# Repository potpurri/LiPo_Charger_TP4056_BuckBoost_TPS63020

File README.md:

# Lithium Battery Charger and Boost Converter PCB

This PCB is designed to safely charge a lithium-ion cell and provide a selectable 3.3V or 5V output. It's equipped with components that ensure safe charging and protection for the battery and supports flexible output and charging options. 

## Features

- **Charging IC**: TP4056 with adjustable charge currents.
- **Protection Circuitry**: DW01A and F8205A provide overcharge, over-discharge, and overcurrent protection.
- **Buck-Boost Converter**: TPS63020 for stable 3.3V or 5V output, selectable via solder jumper.
- **Compact Design**: Ideal for portable applications, with both top and bottom images of the board for easy identification.
- **Fuse Protection**: Added fuse for enhanced safety of the battery connection.
- **Battery disconnection during charging**: When the USB-C port is connected for charging, the battery is disconnected from the Buck-Boost converter via two p-channel MOSFETs in series, with the gates tied to VBUS of the USB-C input. Power is instead provided to the Buck-Boost converter using a Schottky diode during charging. This circuit can be bypassed using the solder jumper on the bottom side of the PCB.

## Charging Current Settings

The charging current of the TP4056 can be adjusted using solder jumpers on the PCB to meet various requirements. Refer to the table below:

| Solder Jumper Setting | Charging Current |
|-----------------------|------------------|
| J1                    | 130 mA           |
| J2                    | 280 mA           |
| J3                    | 400 mA           |
| J4                    | 580 mA           |
| J5                    | 780 mA           |
| J6                    | 1000 mA          |

## Images

### Schematic

### 3D Renderings
- Front View: 
- Front View Without Components: 
- Back View: 

### PCB
**4-Layer Stackup**: Signal Layer, GND Layer, Power Layer, Signal Layer
- All layers: 
- Front traces: 
- GND plane: 
- PWR plane: 
- Back traces: 

## Usage

1. **Output Voltage Selection**: Set the desired output voltage (3.3V or 5V) by configuring the solder jumper on the PCB.
2. **Charging Current Selection**: Set the charging current by adjusting the appropriate solder jumper(s) according to the table above.
3. **Connect Battery**: Connect the lithium-ion cell to the battery terminals.
4. **Power Input**: Provide power via the charging input, and the circuit will manage safe charging for the battery and maintain output stability.
5. **Fuse Protection**: Ensure the fuse is correctly in place for additional battery safety.
6. **Battery disconnection during charging**: When the USB-C port is connected, the battery is safely disconnected from the Buck-Boost converter, and power is instead supplied to it from VBUS through a Schottky diode.

---

This board is ideal for applications needing a stable 3.3V or 5V from a lithium-ion cell with enhanced safety and flexibility. With the added features, it provides even more robust protection and usability for various portable electronic projects.

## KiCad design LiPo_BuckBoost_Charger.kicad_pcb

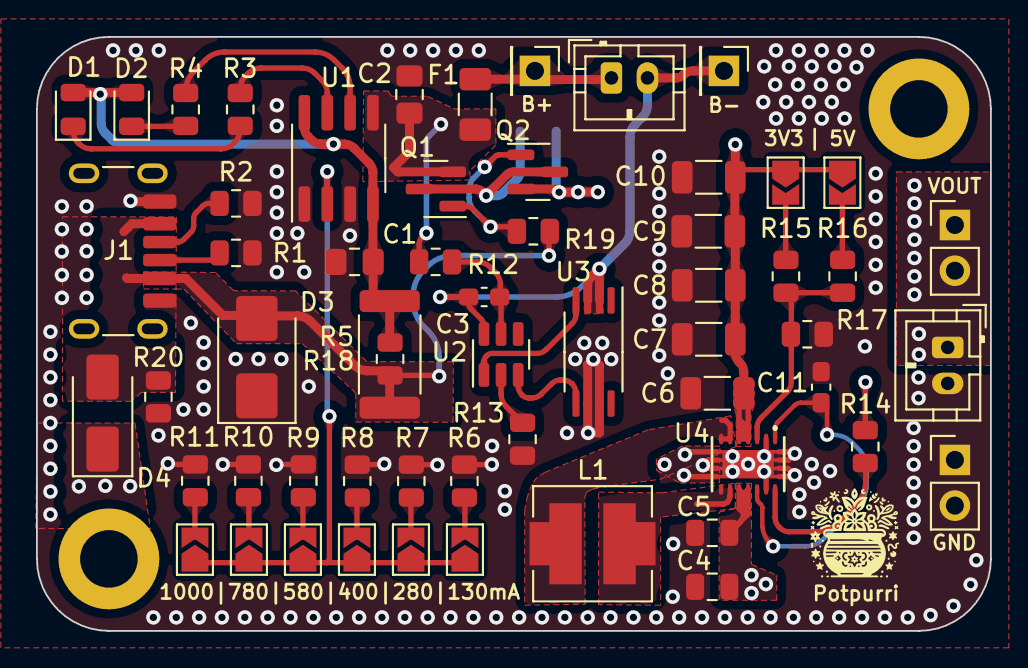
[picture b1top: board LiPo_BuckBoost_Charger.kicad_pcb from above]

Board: 4 copper layers, 53.0 x 33.0 mm, 61 parts (1 on the bottom side), 34 nets.

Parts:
C1, C2: 10u; C_0805_2012Metric_Pad1.18x1.45mm_HandSolder
C3, C11: 100n; C_0603_1608Metric_Pad1.08x0.95mm_HandSolder
C4, C5: 10u; C_0805_2012Metric
C6, C7, C8, C9: 22u; C_1206_3216Metric
C10: 100u; C_1206_3216Metric
D1: RED; D_0805_2012Metric
D2: GREEN; D_0805_2012Metric
D3: SMBJ12CA; D_SMB
D4: SS34; D_SMA
F1: 1.5A; Fuse_1206_3216Metric
H1, H2: MountingHole; MountingHole_3.2mm_M3_DIN965_Pad
J1: Type-C_6P; USB-C 6 Pin - Long pads
J2, J5: JST PH Connector; JST_PH_B2B-PH-K_1x02_P2.00mm_Vertical
J3, J4: Conn_01x01; PinHeader_1x01_P2.54mm_Vertical
J6, J7: JST PH Connector; PinHeader_1x02_P2.54mm_Vertical
JP1, JP2, JP3, JP4, JP5, JP6, JP7, JP8: SolderJumper_2_Open; SolderJumper-2_P1.3mm_Open_TrianglePad1.0x1.5mm
JP9: SolderJumper_3_Open; SolderJumper-3_P2.0mm_Open_TrianglePad1.0x1.5mm
L1: 2u2; Combined CD43 + L 6.3x6.3
Q1, Q2: SI2301; SOT-23
R1, R2: 5k1; R_0805_2012Metric
R3, R4, R13: 1k; R_0805_2012Metric
R5: 0R4; R_0805_2012Metric
R6, R20: 10k; R_0805_2012Metric
R7: 4k7; R_0805_2012Metric
R8: 3k; R_0805_2012Metric
R9: 2k; R_0805_2012Metric
R10: 1k5; R_0805_2012Metric
R11: 1k2; R_0805_2012Metric
R12: 100R; R_0805_2012Metric
R14, R15: 1M; R_0805_2012Metric
R16: 1M6; R_0805_2012Metric
R17: 180k; R_0805_2012Metric
R18: 2512 package; R_2512_6332Metric
R19: R; R_0805_2012Metric
U1: TP4056; SOP-8_3.76x4.96mm_P1.27mm
U2: DW01A; SOT-23-6
U3: FS8205A; TSSOP-8_4.4x3mm_P0.65mm
U4: TPS63020; QFN14-3X4MM

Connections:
+5V: C6.1, C7.1, C8.1, C9.1, C10.1, J5.1, J6.1, J6.2, JP7.1 (A), JP8.1 (A), R14.1, U4.4 (VOUT), U4.5 (VOUT)
+BATT: F1.1, J2.1, J3.1
-BATT: C3.2, J2.2, J4.1, U2.6 (GND), U3.2 (S1), U3.3 (S1)
GND: C1.2, C2.2, C4.2, C5.2, C6.2, C7.2, C8.2, C9.2, C10.2, C11.2, D3.1 (A1), J1.A12 (GND), J1.B12 (GND), J5.2, J7.1, J7.2, R1.2, R2.2, R6.2, R7.2, R8.2, R9.2, R10.2, R11.2, R13.2, R17.2, R20.2, U1.1 (TEMP), U1.3 (GND), U3.6 (S2), U3.7 (S2), U4.2 (GND), U4.13 (PS/SYNC), U4.15 (PGND), U4.16 (PGND), U4.17 (PGND), U4.18 (PGND), U4.19 (PGND), U4.20 (PGND), U4.21 (PGND), U4.22 (PGND), U4.23 (PGND)
unnamed: C1.1, D1.2 (A), D2.2 (A), R5.1, R18.1, U1.4 (VCC), U1.8 (CE)
unnamed: D1.1 (K), R3.1
unnamed: D2.1 (K), R4.1
unnamed: J1.A5 (CC1), R2.1
unnamed: J1.B5 (CC2), R1.1
unnamed: JP1.1 (A), JP2.1 (A), JP3.1 (A), JP4.1 (A), JP5.1 (A), JP6.1 (A), U1.2 (PROG)
unnamed: JP1.2 (B), R6.1
unnamed: JP2.2 (B), R7.1
unnamed: JP3.2 (B), R8.1
unnamed: JP4.2 (B), R9.1
unnamed: JP5.2 (B), R10.1
unnamed: JP6.2 (B), R11.1
unnamed: JP7.2 (B), R15.1
unnamed: JP8.2 (B), R16.1
unnamed: C2.1, F1.2, JP9.1 (A), Q1.2 (S), R12.2, U1.5 (BAT)
unnamed: JP9.2 (C), Q1.3 (D), Q2.3 (D)
unnamed: L1.1, U4.8 (L1), U4.9 (L1)
unnamed: L1.2, U4.6 (L2), U4.7 (L2)
unnamed: Q1.1 (G), Q2.1 (G), R19.1
unnamed: R3.2, U1.7 (CHRG)
unnamed: R4.2, U1.6 (STDBY)
unnamed: U2.3 (OC), U3.5 (G2)
unnamed: U2.1 (OD), U3.4 (G1)
unnamed: C3.1, R12.1, U2.5 (VCC)
unnamed: R13.1, U2.2 (VM)
unnamed: C11.1, U4.1 (VINA), U4.12 (EN)
unnamed: R15.2, R16.2, R17.1, U4.3 (FB)
unnamed: R14.2, U4.14 (PG)
VBUS: D3.2 (A2), D4.2 (A), J1.A9 (VBUS), J1.B9 (VBUS), R5.2, R18.2, R19.2, R20.1
VCC: C4.1, C5.1, D4.1 (K), JP9.3 (B), Q2.2 (S), U4.10 (VIN), U4.11 (VIN)

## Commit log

2024-11-04 Schematic and component placing done
2024-11-04 added schematic and 3d img
2024-11-04 some traces and gnd vias
2024-11-05 Pcb traces and layout done
2024-11-05 schematic update, added imgs
2024-11-05 added readme.md
2024-11-05 minor change to readme
2024-11-05 readme
2024-11-05 added fillet tracks and tear drops to pcb
2024-11-05 Version 1.1 - added 2512 footprint for input resistor to TP4056
2024-11-05 change img name
2024-11-07 Added jlc serial number silk screen
2024-11-10 v1.2, fixed filled zones for inductor
2024-11-11 added pmos circuit to disconnect battery from load during charging
2024-11-13 version 1.3 - added circuit which disconnects battery from load during charging
2024-11-13 updated version number on pcb, updated readme
2024-12-16 minor adjustments
2024-12-16 added gerbers
2024-12-27 fixed faulty schematic link in readme
